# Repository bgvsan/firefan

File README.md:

Fire Fan
=======

A minimal board for your Fire, manage temperature and 220 Volt Fan.

File Available
=======

-- Eagle Pcb Files (schematics, board, gerber)
-- Microcontroller source code and Hex file
-- Bom list

License
=====
See [License] (LICENSE) file.

Support
======
For any problem or support request mail to me[@]diegosantinelli.it

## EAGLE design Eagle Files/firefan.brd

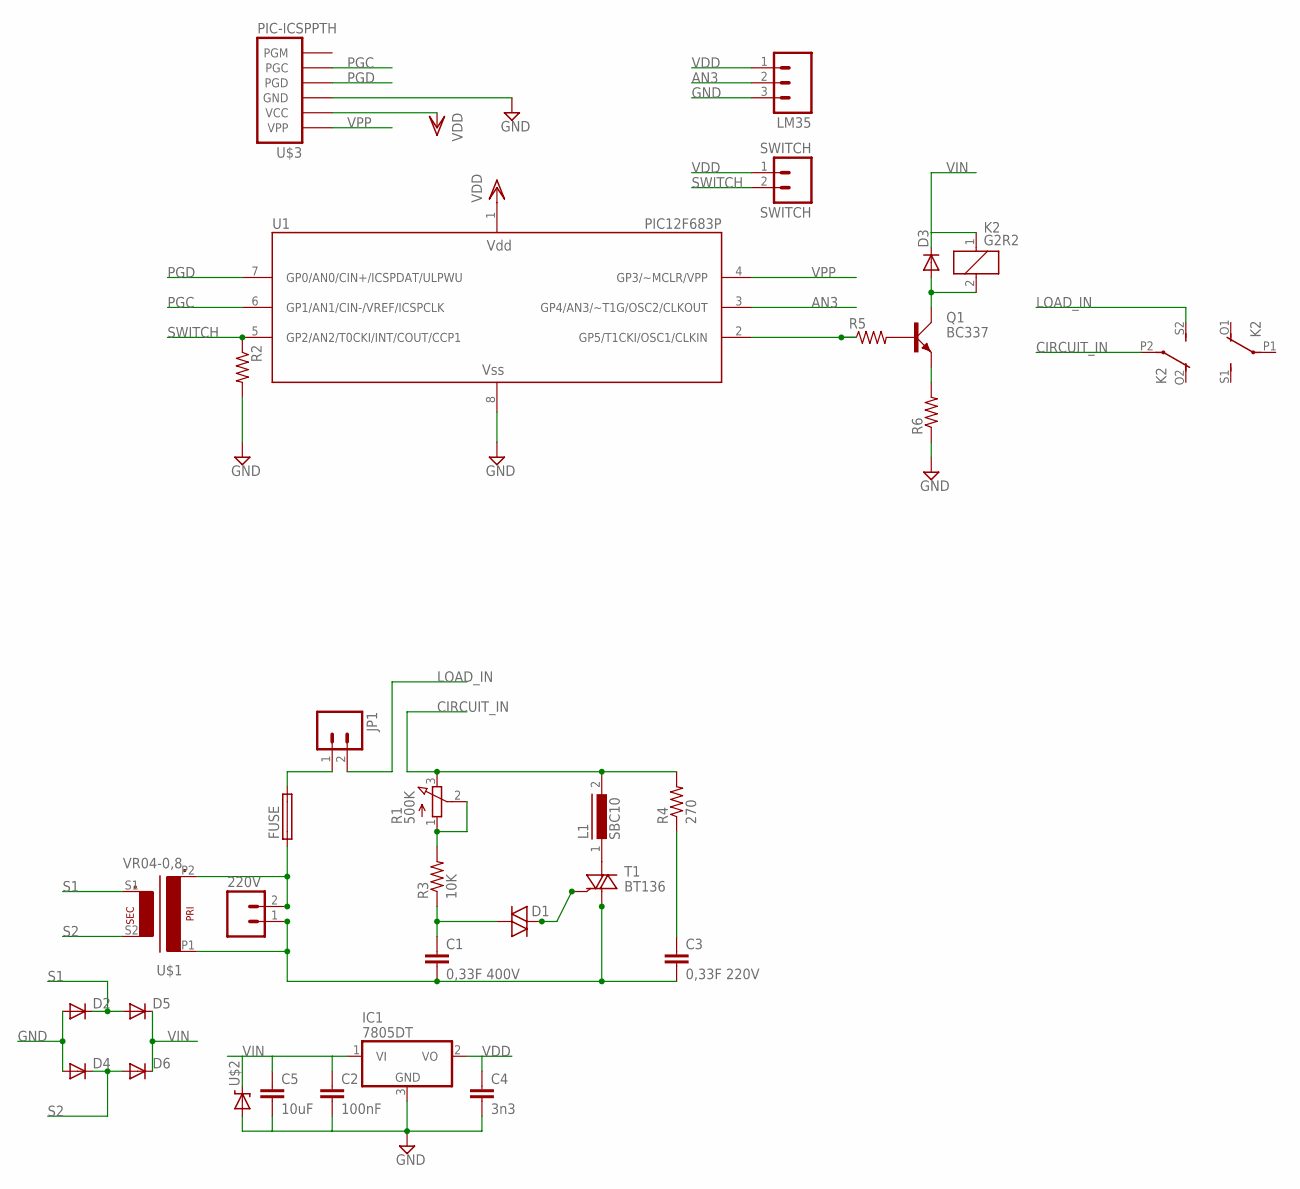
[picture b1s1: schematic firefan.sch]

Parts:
220V: M023.5MM-NO_SILK; SCREWTERMINAL-3.5MM-2-NS
C1: 0,33F 400V; CAP-PTH-5MM
C2: 100nF; CAP-PTH-5MM
C3: 0,33F 220V; CAP-PTH-5MM
C4: 3n3; CAP-PTH-5MM
C5: 10uF; CAP-PTH-5MM
D1: DIAC-DO35-10; DO35-10
D2, D3, D4, D5, D6: 1N4004; DO41-10
FUSE: SH22,5A
IC1: 7805DT; TO252
JP1: M023.5MM-NO_SILK; SCREWTERMINAL-3.5MM-2-NS
K2: G2R2
L1: SBC10
LM35: M03LONGPADS; 1X03_LONGPADS
Q1: BC337; SOT54A
R1: 500K; 3RP/1610N
R2, R5, R6: RESISTORPTH-1/4W; AXIAL-0.4
R3: 10K; AXIAL-0.5
R4: 270; AXIAL-0.5
SWITCH: SWITCH; SCREWTERMINAL-3.5MM-2-NS
T1: BT136; TO220AB
U1: PIC12F683P; DIP-8
U$1: VR04-0,8
U$2: DIODE-ZENERPTH; DIODE-ZENER
U$3: PIC-ICSPPTH; MOLEX-1X6

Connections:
AN3: LM35.2, U1.3 (GP4/AN3/~T1G/OSC2/CLKOUT)
CIRCUIT_IN: K2.P2, L1.2, R1.3 (E), R4.P$2 (2)
GND: C2.2, C4.2, C5.2, D2.A, D4.A, IC1.3 (GND), LM35.3, R2.P$2 (2), R6.P$1 (1), U1.8 (VSS), U$2.P$2 (A), U$3.3 (GND)
LOAD_IN: JP1.2, K2.S2 (S)
unnamed: FUSE.2, JP1.1
unnamed: D1.C (2), T1.3 (G)
unnamed: R1.1 (A), R1.2 (S), R3.P$2 (2)
unnamed: L1.1, T1.2 (A2)
unnamed: C1.1, D1.A (1), R3.P$1 (1)
unnamed: C3.1, R4.P$1 (1)
unnamed: 220V.1, C1.2, C3.2, T1.1 (A1), U$1.P1
unnamed: 220V.2, FUSE.1, U$1.P2
unnamed: Q1.B, R5.P$2 (2)
unnamed: Q1.E, R6.P$2 (2)
unnamed: D3.A, K2.2, Q1.C
PGC: U1.6 (GP1/AN1/CIN-/VREF/ICSPCLK), U$3.5 (PGC)
PGD: U1.7 (GP0/AN0/CIN+/ICSPDAT/ULPWU), U$3.4 (PGD)
RELAIS: R5.P$1 (1), U1.2 (GP5/T1CKI/OSC1/CLKIN)
S1: D2.C, D5.A, U$1.S1 (S3)
S2: D4.C, D6.A, U$1.S2 (S4)
SWITCH: R2.P$1 (1), SWITCH.2, U1.5 (GP2/AN2/T0CKI/INT/COUT/CCP1)
VDD: C4.1, IC1.2 (VO), LM35.1, SWITCH.1, U1.1 (VDD), U$3.2 (VCC)
VIN: C2.1, C5.1, D3.C, D5.C, D6.C, IC1.1 (VI), K2.1, U$2.P$1 (C)
VPP: U1.4 (GP3/~MCLR/VPP), U$3.1 (VPP)

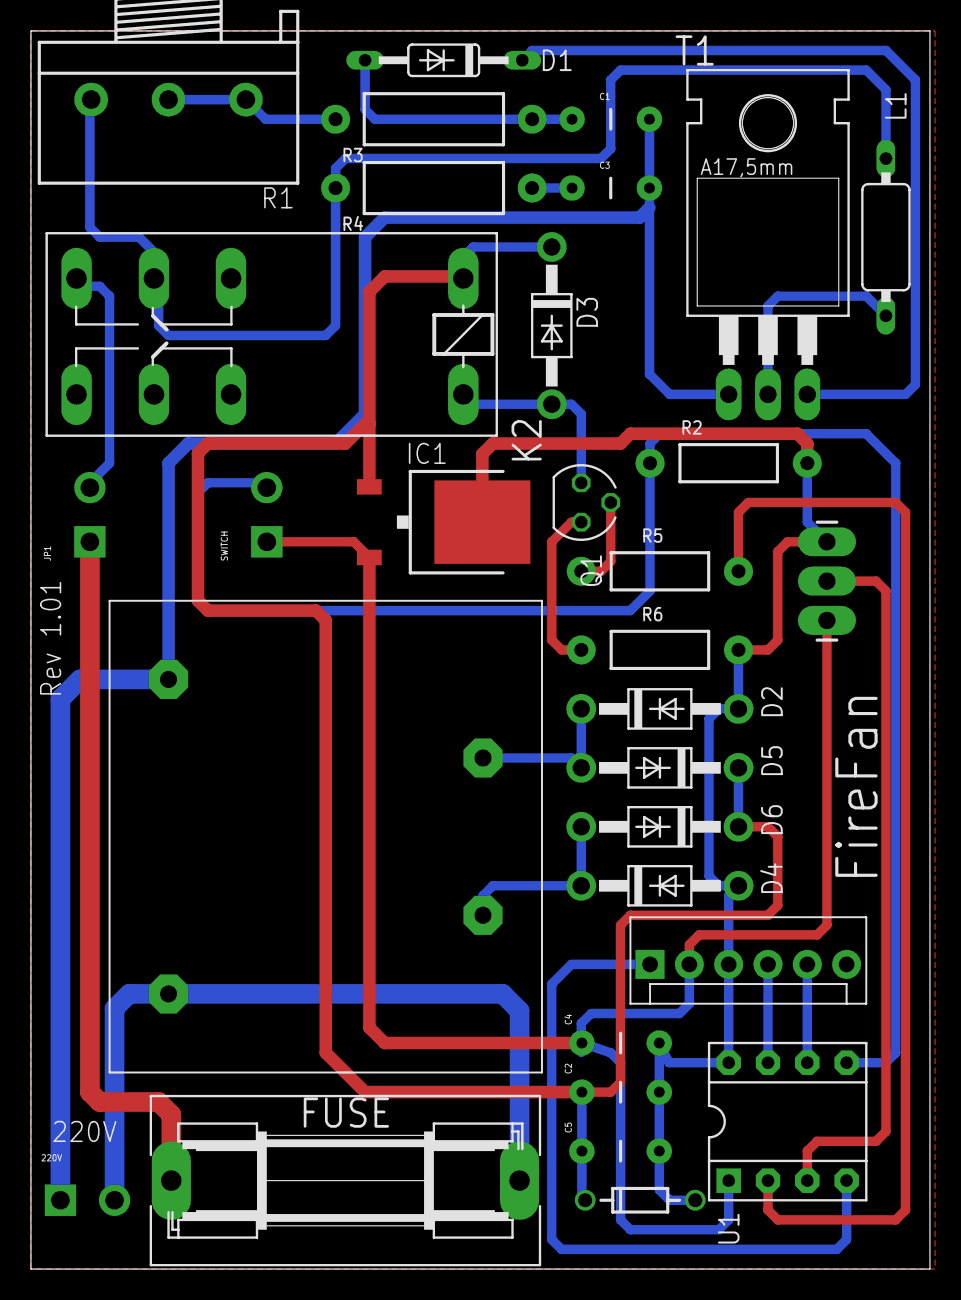
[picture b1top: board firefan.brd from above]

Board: 4 copper layers, 58.1 x 80.0 mm, 31 parts (0 on the bottom side), 24 nets.

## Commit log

2014-04-25 main project update
2014-06-27 finished and tested
2014-07-04 Add eagle file board & schematics Ver 1.01
2014-07-05 Readme and license add

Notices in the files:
parts and their libraries:
SparkFun-Resistors: Licensing: CC v3.0 Share-Alike You are welcome to use this library for commercial purposes.
